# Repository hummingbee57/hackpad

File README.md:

# hackpad
hackpad for hackclub blueprint
4x3 number pad with EC11 rotary encoder and RGB underglow

## PCB

PCB design

Schematic for the hackpad

## Case Design

## Bill Of Materials

* 1x unsoldered Seeed XIAO RP2040
* 13x through-hole 1N4148 Diodes
* 12 MX-Style switches
* 1x EC11 Rotary encoders
* 12x white blank DSA keycaps
* 12x SK6812 MINI-E LEDs
* 4x M3x16mm screws
* 4x M3x5mx4mm heatset inserts

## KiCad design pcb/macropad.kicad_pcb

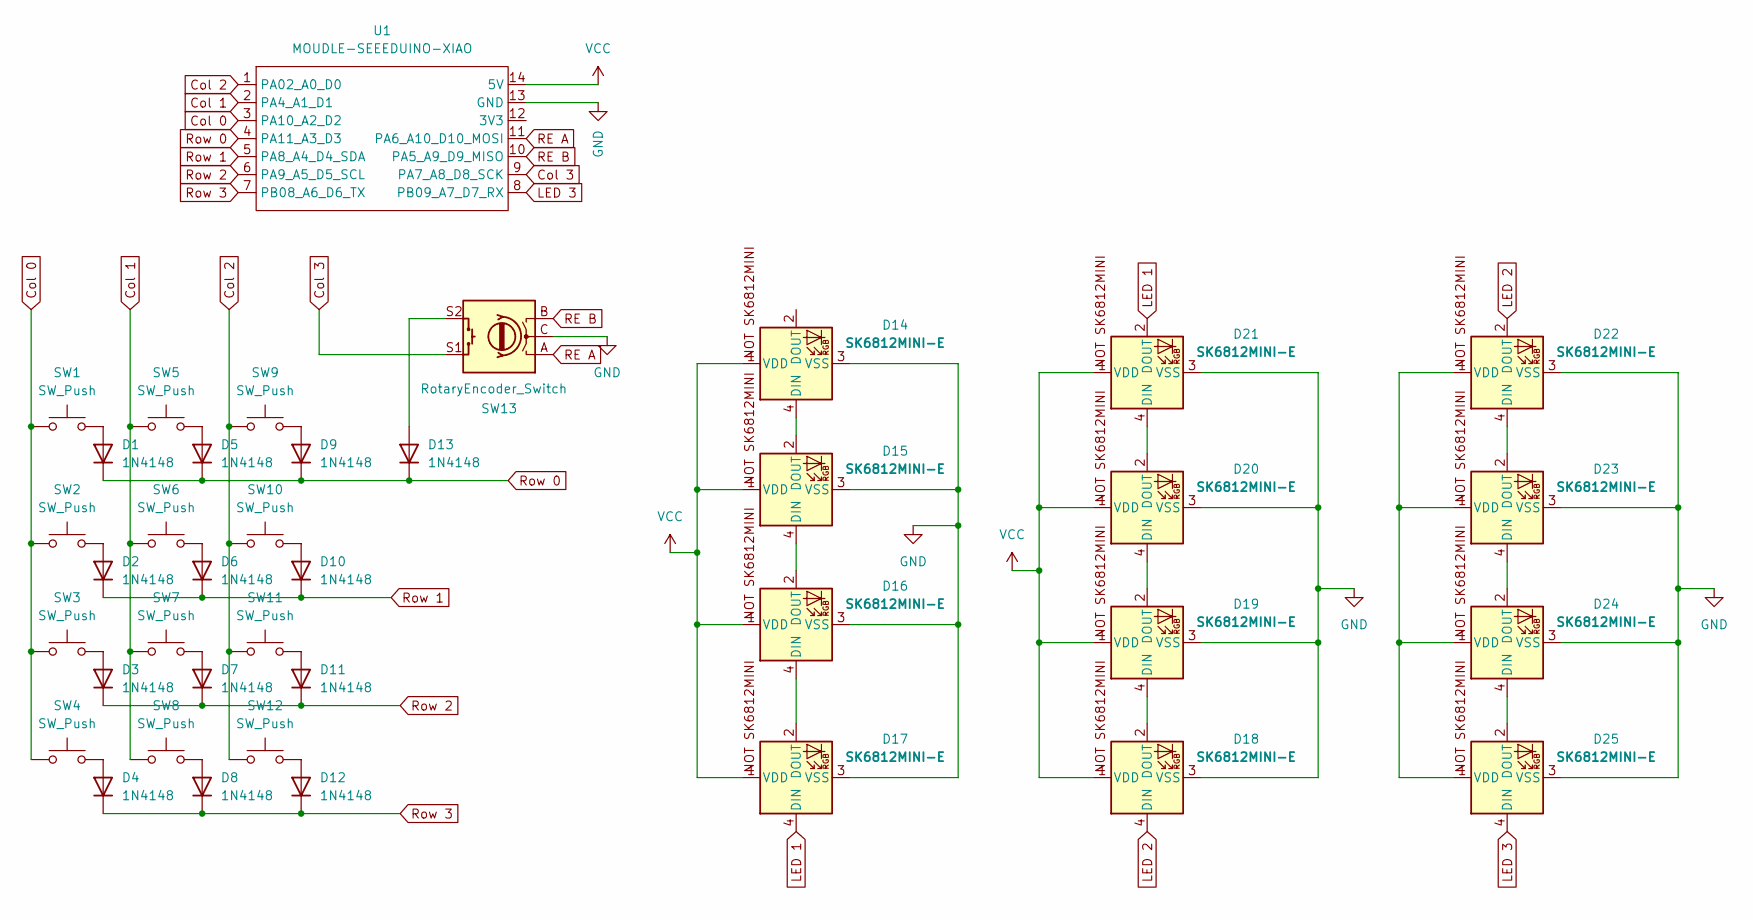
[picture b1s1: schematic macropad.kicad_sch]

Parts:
D1, D2, D3, D4, D5, D6, D7, D8, D9, D10, D11, D12, D13: 1N4148; D_DO-35_SOD27_P7.62mm_Horizontal
D14, D15, D16, D17, D18, D19, D20, D21, D22, D23, D24, D25: SK6812MINI-E; SK6812MINI-E_fixed
SW1, SW2, SW3, SW4, SW5, SW6, SW7, SW8, SW9, SW10, SW11, SW12: SW_Push; SW_Cherry_MX_1.00u_PCB
SW13: RotaryEncoder_Switch; RotaryEncoder_Alps_EC11E-Switch_Vertical_H20mm
U1: MOUDLE-SEEEDUINO-XIAO; XIAO-Generic-Hybrid-14P-2.54-21X17.8MM

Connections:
Col 0: SW1.1, SW2.1, SW3.1, SW4.1, U1.3 (PA10_A2_D2)
Col 1: SW5.1, SW6.1, SW7.1, SW8.1, U1.2 (PA4_A1_D1)
Col 2: SW9.1, SW10.1, SW11.1, SW12.1, U1.1 (PA02_A0_D0)
Col 3: SW13.S1, U1.9 (PA7_A8_D8_SCK)
GND: D14.3 (VSS), D15.3 (VSS), D16.3 (VSS), D17.3 (VSS), D18.3 (VSS), D19.3 (VSS), D20.3 (VSS), D21.3 (VSS), D22.3 (VSS), D23.3 (VSS), D24.3 (VSS), D25.3 (VSS), SW13.C, U1.13 (GND)
LED 1: D17.4 (DIN), D21.2 (DOUT)
LED 2: D18.4 (DIN), D22.2 (DOUT)
LED 3: D25.4 (DIN), U1.8 (PB09_A7_D7_RX)
unnamed: D1.2 (A), SW1.2
unnamed: D2.2 (A), SW2.2
unnamed: D3.2 (A), SW3.2
unnamed: D4.2 (A), SW4.2
unnamed: D5.2 (A), SW5.2
unnamed: D6.2 (A), SW6.2
unnamed: D7.2 (A), SW7.2
unnamed: D8.2 (A), SW8.2
unnamed: D9.2 (A), SW9.2
unnamed: D10.2 (A), SW10.2
unnamed: D11.2 (A), SW11.2
unnamed: D12.2 (A), SW12.2
unnamed: D13.2 (A), SW13.S2
unnamed: D14.4 (DIN), D15.2 (DOUT)
unnamed: D15.4 (DIN), D16.2 (DOUT)
unnamed: D16.4 (DIN), D17.2 (DOUT)
unnamed: D18.2 (DOUT), D19.4 (DIN)
unnamed: D19.2 (DOUT), D20.4 (DIN)
unnamed: D20.2 (DOUT), D21.4 (DIN)
unnamed: D22.4 (DIN), D23.2 (DOUT)
unnamed: D22.1 (VDD), D23.1 (VDD), D24.1 (VDD), D25.1 (VDD)
unnamed: D23.4 (DIN), D24.2 (DOUT)
unnamed: D24.4 (DIN), D25.2 (DOUT)
RE A: SW13.A, U1.11 (PA6_A10_D10_MOSI)
RE B: SW13.B, U1.10 (PA5_A9_D9_MISO)
Row 0: D1.1 (K), D5.1 (K), D9.1 (K), D13.1 (K), U1.4 (PA11_A3_D3)
Row 1: D2.1 (K), D6.1 (K), D10.1 (K), U1.5 (PA8_A4_D4_SDA)
Row 2: D3.1 (K), D7.1 (K), D11.1 (K), U1.6 (PA9_A5_D5_SCL)
Row 3: D4.1 (K), D8.1 (K), D12.1 (K), U1.7 (PB08_A6_D6_TX)
VCC: D14.1 (VDD), D15.1 (VDD), D16.1 (VDD), D17.1 (VDD), D18.1 (VDD), D19.1 (VDD), D20.1 (VDD), D21.1 (VDD), U1.14 (5V)

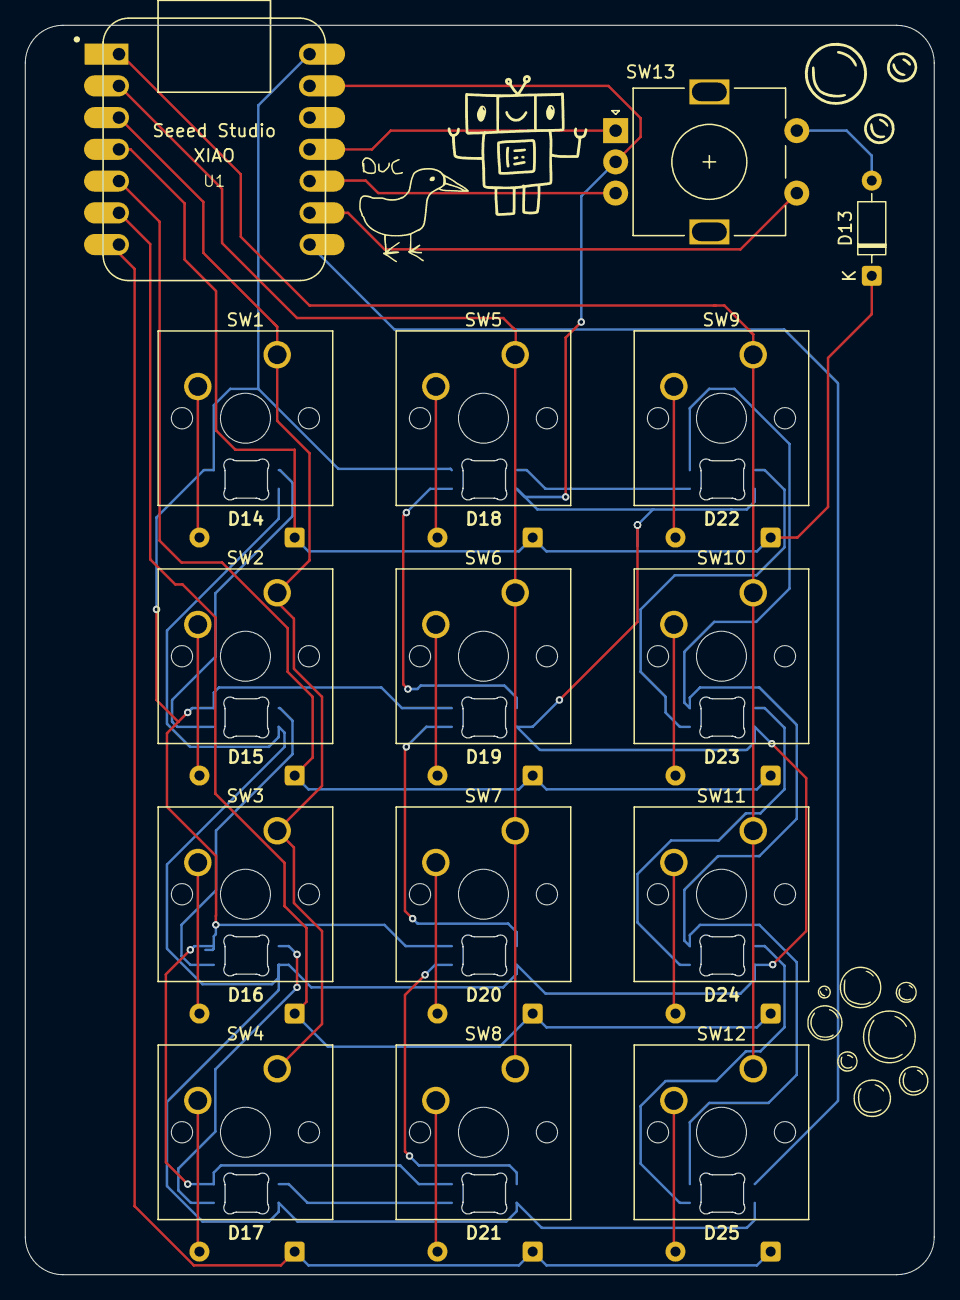
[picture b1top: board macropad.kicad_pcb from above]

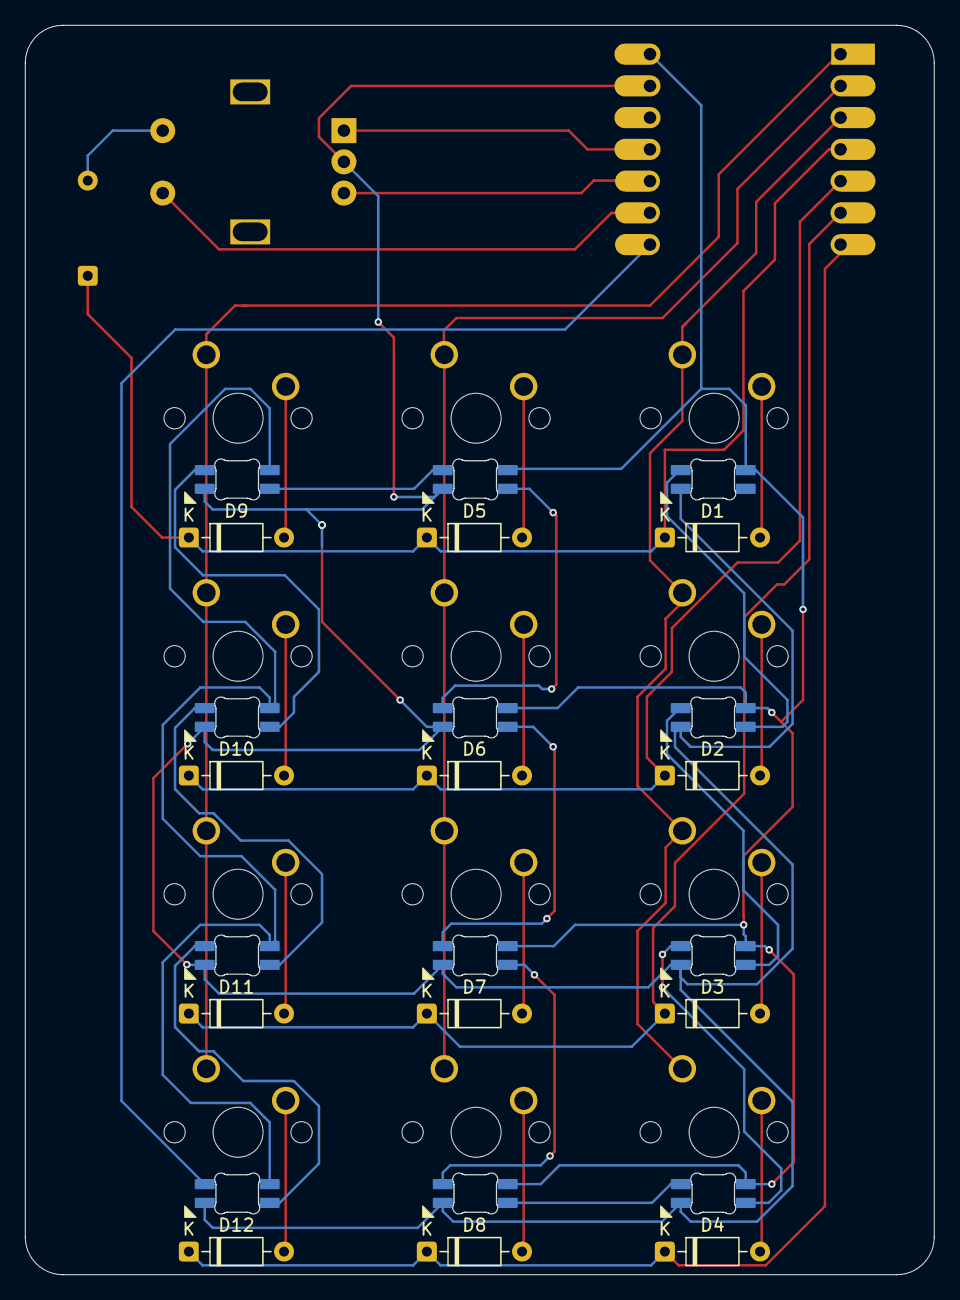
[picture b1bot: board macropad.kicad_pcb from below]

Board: 2 copper layers, 72.7 x 99.9 mm, 39 parts (12 on the bottom side), 38 nets.

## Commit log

2026-03-23 Uploading files to github for submission :D
2026-03-27 updating files
2026-03-29 added updated bottom
